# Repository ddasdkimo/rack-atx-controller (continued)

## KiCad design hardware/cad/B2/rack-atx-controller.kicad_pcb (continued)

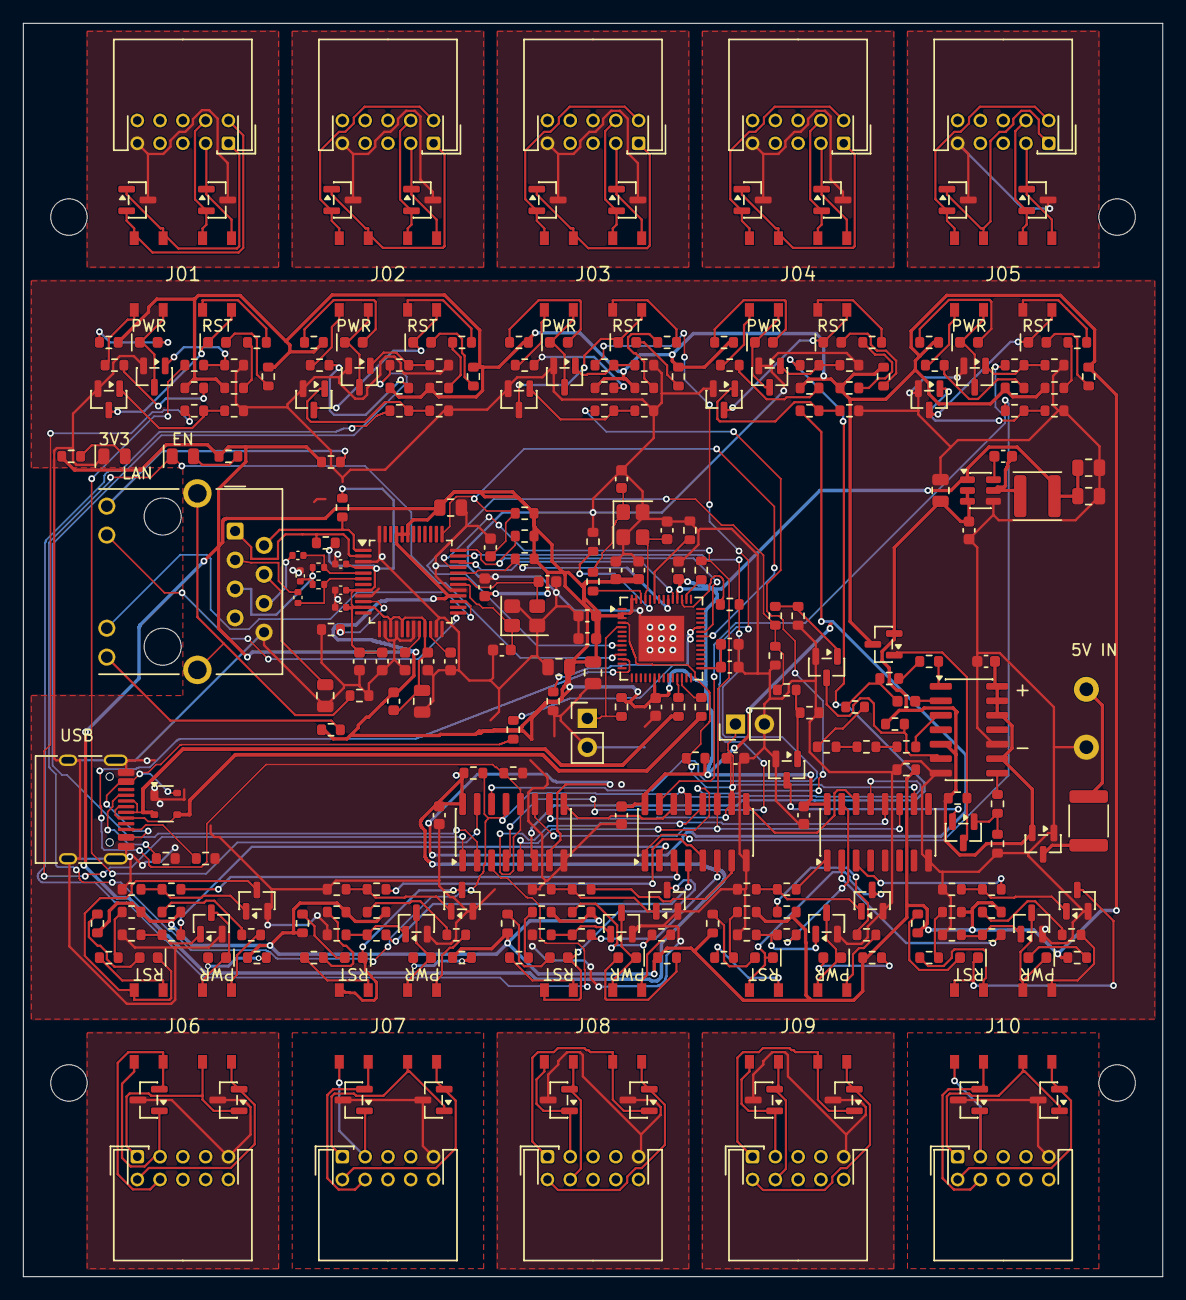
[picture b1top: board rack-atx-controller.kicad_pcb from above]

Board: 2 copper layers, 100.0 x 110.0 mm, 304 parts (0 on the bottom side), 243 nets.

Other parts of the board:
MH1, MH2, MH3, MH4: MountingHole_3.2mm_M3

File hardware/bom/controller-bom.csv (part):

Designator,Quantity per board,Comment,Manufacturer,MPN,LCSC Part #,Package,Footprint candidate,Library class,Assembly,PCBA mode,Observed stock,Checked at UTC,Source,Notes
J101,1,WJ500V-5.08-2P,Ningbo Kangnex Elec,WJ500V-5.08-2P,C8465,"Plugin,P=5.08mm",RackATX:WJ500V_5.08_2P,Extended,Wave Soldering,Economic and Standard,261906,2026-10-13T15:48:15.997975+00:00,https://jlcpcb.com/partdetail/C8465,Drawing/library candidate used in S.3; physical footprint and assembly DFM qualification pending.
F1,1,MF-MSMF150/24X-2 1.5A,BOURNS,MF-MSMF150/24X-2,C78695,1812,Fuse:Fuse_1812_4532Metric,Extended,SMT Assembly,Economic and Standard,6223,2026-10-13T15:22:31.648916+00:00,https://jlcpcb.com/partdetail/C78695,
"Q1,Q4",2,AO3401A,Alpha & Omega Semicon,AO3401A,C15127,SOT-23,Package_TO_SOT_SMD:SOT-23,Basic,SMT Assembly,Economic and Standard,631158,2026-10-13T15:24:52.156424+00:00,https://jlcpcb.com/partdetail/C15127,
"C1,C14,C15,C27,C29",5,10u,Samsung Electro-Mechanics,CL21A106KAYNNNE,C15850,0805,Capacitor_SMD:C_0805_2012Metric,Basic,SMT Assembly,Economic and Standard,4003857,2026-10-13T15:20:39.544599+00:00,https://jlcpcb.com/partdetail/C15850,
"C2,C3,C6,C8,C9,C10,C11,C12,C13,C21,C22,C23,C24,C25,C26,C28,C37,C38,C39,C42",20,100n,YAGEO,CC0603KRX7R9BB104,C14663,0603,Capacitor_SMD:C_0603_1608Metric,Basic,SMT Assembly,Economic and Standard,53307896,2026-10-13T15:20:39.536320+00:00,https://jlcpcb.com/partdetail/C14663,
U1,1,AP63203WU-7,Diodes Incorporated,AP63203WU-7,C780769,TSOT-23-6,Package_TO_SOT_SMD:TSOT-23-6,Extended,SMT Assembly,Economic and Standard,8099,2026-10-13T15:15:58.092399+00:00,https://jlcpcb.com/partdetail/C780769,
L1,1,4.7uH FNR4018S4R7MT,cjiang (Changjiang Microelectronics Tech),FNR4018S4R7MT,C167806,"SMD,4x4mm",Inductor_SMD:L_Changjiang_FNR4018S,Extended,SMT Assembly,Economic and Standard,7188,2026-10-13T15:18:09.856125+00:00,https://jlcpcb.com/partdetail/C167806,Drawing/library candidate used in S.3; physical footprint and assembly DFM qualification pending.
"C4,C5",2,22u,Samsung Electro-Mechanics,CL21A226MAQNNNE,C45783,0805,Capacitor_SMD:C_0805_2012Metric,Basic,SMT Assembly,Economic and Standard,3454275,2026-10-13T15:15:59.158144+00:00,https://jlcpcb.com/partdetail/C45783,
U2,1,ESP32-S3FN8,Espressif Systems,ESP32-S3FN8,C2913196,QFN-56-EP(7x7),Package_DFN_QFN:QFN-56-1EP_7x7mm_P0.4mm_EP4x4mm,Extended,SMT Assembly,Economic and Standard,2345,2026-10-13T15:12:40.649680+00:00,https://jlcpcb.com/partdetail/C2913196,
"C7,C16,C30",3,1u,Samsung Electro-Mechanics,CL10A105KB8NNNC,C15849,0603,Capacitor_SMD:C_0603_1608Metric,Basic,SMT Assembly,Economic and Standard,10311730,2026-10-13T15:46:51.366149+00:00,https://jlcpcb.com/partdetail/C15849,
"R1,R2,R3,R4,R15,R16,R17,R25,R27,R28,R30,R33,R37,R35,R36",15,10k 1%,UNI-ROYAL(Uniroyal Elec),0603WAF1002T5E,C25804,0603,Resistor_SMD:R_0603_1608Metric,Basic,SMT Assembly,Economic and Standard,31975394,2026-10-13T15:10:20.790070+00:00,https://jlcpcb.com/partdetail/C25804,
"J102,J103",2,PZ254V-11-02P,XFCN,PZ254V-11-02P,C492401,"Plugin,P=2.54mm",Connector_PinHeader_2.54mm:PinHeader_1x02_P2.54mm_Vertical,Extended,Wave Soldering,Economic and Standard,1143383,2026-10-13T15:31:20.503576+00:00,https://jlcpcb.com/partdetail/C492401,
Y1,1,40MHz CL12pF,YXC Crystal Oscillators,XL2EL89COI-111YLC-40M,C18214314,SMD3225-4P,Crystal:Crystal_SMD_3225-4Pin_3.2x2.5mm,Extended,SMT Assembly,Economic and Standard,31425,2026-10-13T15:20:35.889069+00:00,https://jlcpcb.com/partdetail/C18214314,
"R5,R24",2,0 1%,UNI-ROYAL(Uniroyal Elec),0603WAF0000T5E,C21189,0603,Resistor_SMD:R_0603_1608Metric,Basic,SMT Assembly,Economic and Standard,24624745,2026-10-13T15:20:39.483336+00:00,https://jlcpcb.com/partdetail/C21189,
"C17,C18,C31,C32",4,20p,Samsung Electro-Mechanics,CL10C200JB8NNNC,C1648,0603,Capacitor_SMD:C_0603_1608Metric,Basic,SMT Assembly,Economic and Standard,1984484,2026-10-13T15:22:34.155368+00:00,https://jlcpcb.com/partdetail/C1648,
"R6,R7",2,47 1%,UNI-ROYAL(Uniroyal Elec),0603WAF470JT5E,C23182,0603,Resistor_SMD:R_0603_1608Metric,Basic,SMT Assembly,Economic and Standard,971973,2026-10-13T15:11:27.450515+00:00,https://jlcpcb.com/partdetail/C23182,
J104,1,TYPE-C-31-M-12,Korean Hroparts Elec,TYPE-C-31-M-12,C165948,SMD,Connector_USB:USB_C_Receptacle_HRO_TYPE-C-31-M-12,Extended,SMT Assembly,Economic and Standard,398485,2026-10-13T15:11:33.015832+00:00,https://jlcpcb.com/partdetail/C165948,
D1,1,"PRTR5V0U2X,215",Nexperia,"PRTR5V0U2X,215",C12333,SOT-143,Package_TO_SOT_SMD:SOT-143,Extended,SMT Assembly,Economic and Standard,23665,2026-10-13T15:24:52.166312+00:00,https://jlcpcb.com/partdetail/C12333,
"R8,R9",2,5.1k 1%,UNI-ROYAL(Uniroyal Elec),0603WAF5101T5E,C23186,0603,Resistor_SMD:R_0603_1608Metric,Basic,SMT Assembly,Economic and Standard,24076196,2026-10-13T15:22:33.103748+00:00,https://jlcpcb.com/partdetail/C23186,
"R10,R11",2,33 1%,UNI-ROYAL(Uniroyal Elec),0603WAF330JT5E,C23140,0603,Resistor_SMD:R_0603_1608Metric,Basic,SMT Assembly,Economic and Standard,5175876,2026-10-13T15:41:21.024471+00:00,https://jlcpcb.com/partdetail/C23140,
"R12,R13,R26,R29,R31,R32,RT1,RT2,RT3,RT4,R34,R38,R40,R44,R48,R52,R56,R60,R64,R68,R72,R76,R80,R84,R88,R92,R96,R100,R104,R108,R112,R116",32,100k 1%,UNI-ROYAL(Uniroyal Elec),0603WAF1003T5E,C25803,0603,Resistor_SMD:R_0603_1608Metric,Basic,SMT Assembly,Economic and Standard,20296056,2026-10-13T15:11:26.198973+00:00,https://jlcpcb.com/partdetail/C25803,
U3,1,W5500,WIZNET,W5500,C32843,LQFP-48_7x7,Package_QFP:LQFP-48_7x7mm_P0.5mm,Extended,SMT Assembly,Economic and Standard,15204,2026-10-13T15:20:39.517626+00:00,https://jlcpcb.com/partdetail/C32843,
L2,1,120R@100MHz GZ1608D121TF,Sunlord,GZ1608D121TF,C12391,0603,Inductor_SMD:L_0603_1608Metric,Extended,SMT Assembly,Economic and Standard,211674,2026-10-13T15:31:21.203168+00:00,https://jlcpcb.com/partdetail/C12391,
R14,1,12.4k 1%,UNI-ROYAL(Uniroyal Elec),0603WAF1242T5E,C22865,0603,Resistor_SMD:R_0603_1608Metric,Extended,SMT Assembly,Economic and Standard,199175,2026-10-13T15:22:32.998707+00:00,https://jlcpcb.com/partdetail/C22865,
C19,1,4.7u,Samsung Electro-Mechanics,CL10A475KO8NNNC,C19666,0603,Capacitor_SMD:C_0603_1608Metric,Basic,SMT Assembly,Economic and Standard,3207024,2026-10-13T15:24:52.182713+00:00,https://jlcpcb.com/partdetail/C19666,
"C20,C33",2,10n,FH (Guangdong Fenghua Advanced Tech),0603B103K500NT,C57112,0603,Capacitor_SMD:C_0603_1608Metric,Basic,SMT Assembly,Economic and Standard,6247556,2026-10-13T15:22:34.255431+00:00,https://jlcpcb.com/partdetail/C57112,
Y2,1,25MHz CL12pF,YXC Crystal Oscillators,X322525MOB4SI,C9006,SMD3225-4P,Crystal:Crystal_SMD_3225-4Pin_3.2x2.5mm,Basic,SMT Assembly,Economic and Standard,181710,2026-10-13T15:18:09.304055+00:00,https://jlcpcb.com/partdetail/C9006,
"R18,R19,R20,R21",4,49.9 1%,UNI-ROYAL(Uniroyal Elec),0603WAF499JT5E,C23185,0603,Resistor_SMD:R_0603_1608Metric,Basic,SMT Assembly,Economic and Standard,1972323,2026-10-13T15:24:51.215319+00:00,https://jlcpcb.com/partdetail/C23185,
"C34,C35",2,6.8n,FH (Guangdong Fenghua Advanced Tech),0603B682K500NT,C1631,0603,Capacitor_SMD:C_0603_1608Metric,Basic,SMT Assembly,Economic and Standard,196089,2026-10-13T15:24:50.480062+00:00,https://jlcpcb.com/partdetail/C1631,
C36,1,22n,Samsung Electro-Mechanics,CL21B223KBANNNC,C1729,0805,Capacitor_SMD:C_0805_2012Metric,Basic,SMT Assembly,Economic and Standard,325000,2026-10-13T15:24:52.121389+00:00,https://jlcpcb.com/partdetail/C1729,
"R22,R23,R321,R322",4,330 1%,UNI-ROYAL(Uniroyal Elec),0603WAF3300T5E,C23138,0603,Resistor_SMD:R_0603_1608Metric,Basic,SMT Assembly,Economic and Standard,3627090,2026-10-13T15:12:44.845004+00:00,https://jlcpcb.com/partdetail/C23138,
J105,1,HR911105A,HANRUN(Zhongshan HanRun Elec),HR911105A,C12074,Plugin,Connector_RJ:RJ45_Hanrun_HR911105A_Horizontal,Extended,Wave Soldering,Economic and Standard,48875,2026-10-13T15:10:20.801373+00:00,https://jlcpcb.com/partdetail/C12074,
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
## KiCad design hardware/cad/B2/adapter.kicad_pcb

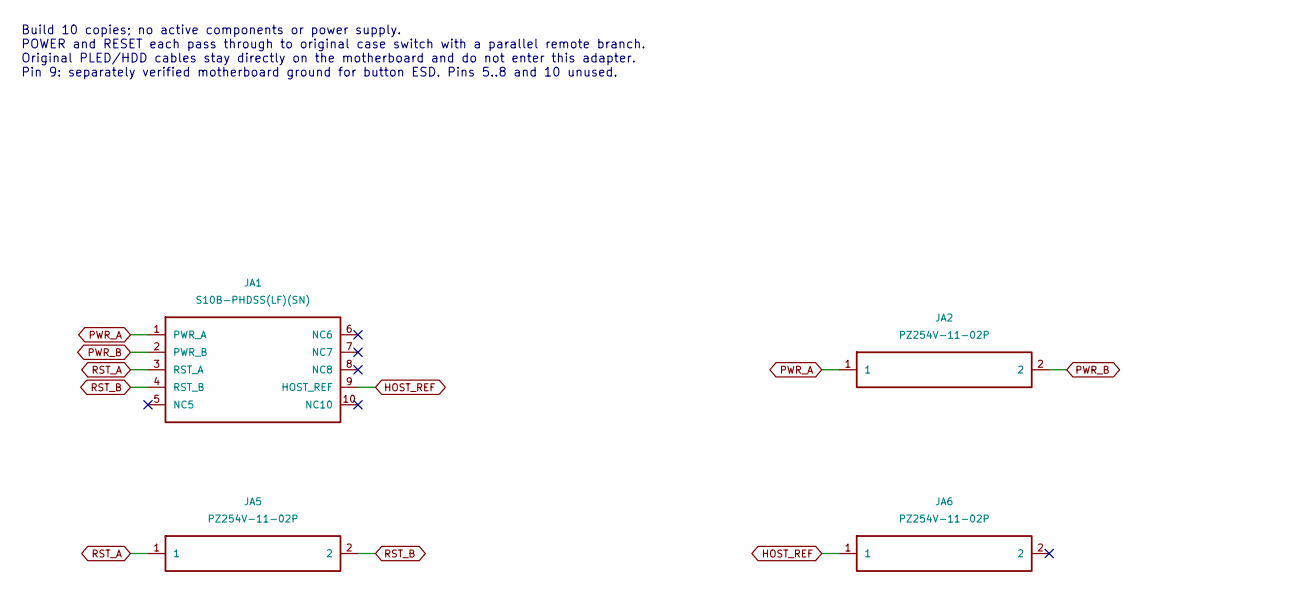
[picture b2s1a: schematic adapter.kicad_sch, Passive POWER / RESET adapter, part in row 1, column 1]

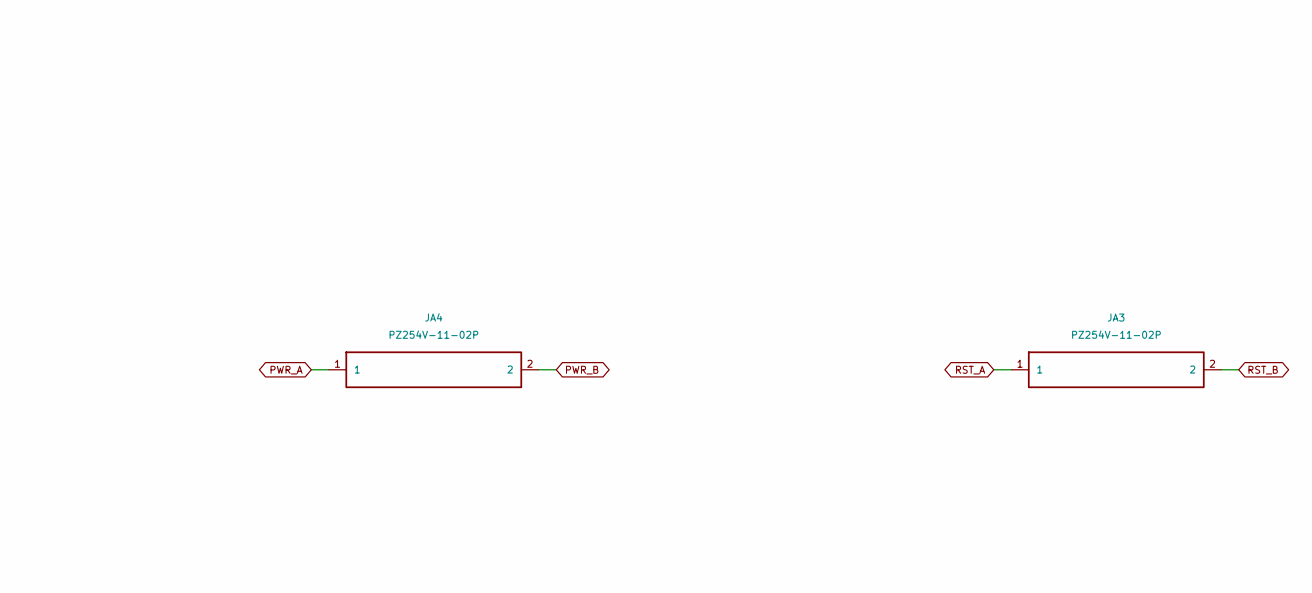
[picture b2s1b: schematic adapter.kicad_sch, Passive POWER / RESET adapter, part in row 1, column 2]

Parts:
JA1: S10B-PHDSS(LF)(SN); JST_PHD_S10B-PHDSS_2x05_P2.00mm_Horizontal; MPN S10B-PHDSS(LF)(SN); LCSC C161672
JA2, JA3, JA4, JA5, JA6: PZ254V-11-02P; PinHeader_1x02_P2.54mm_Vertical; MPN PZ254V-11-02P; LCSC C492401

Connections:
HOST_REF: JA1.9 (HOST_REF), JA6.1
PWR_A: JA1.1 (PWR_A), JA2.1, JA4.1
PWR_B: JA1.2 (PWR_B), JA2.2, JA4.2
RST_A: JA1.3 (RST_A), JA3.1, JA5.1
RST_B: JA1.4 (RST_B), JA3.2, JA5.2

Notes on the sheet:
Build 10 copies; no active components or power supply. POWER and RESET each pass through to original case switch with a parallel remote branch. Original PLED/HDD cables stay directly on the motherboard and do not enter this adapter. Pin 9: separately verified motherboard ground for button ESD. Pins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

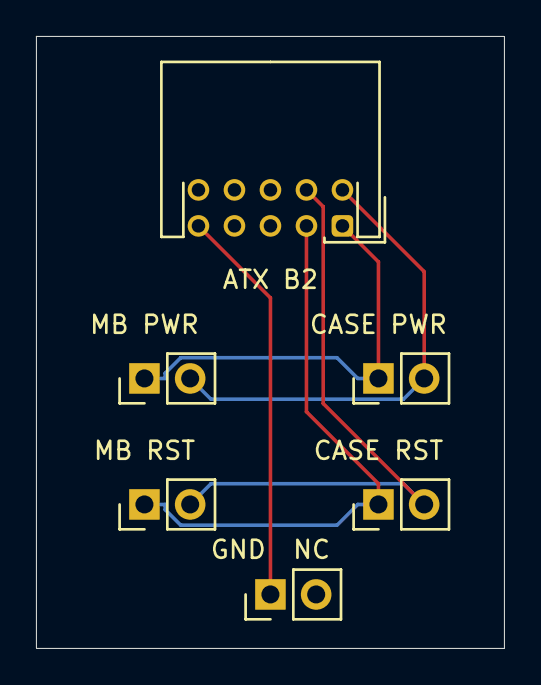
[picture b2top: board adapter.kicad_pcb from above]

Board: 2 copper layers, 26.0 x 34.0 mm, 6 parts (0 on the bottom side), 5 nets.

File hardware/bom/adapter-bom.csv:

Designator,Quantity per board,Comment,Manufacturer,MPN,LCSC Part #,Package,Footprint candidate,Library class,Assembly,PCBA mode,Observed stock,Checked at UTC,Source,Notes
JA1,1,S10B-PHDSS(LF)(SN),JST,S10B-PHDSS(LF)(SN),C161672,"Push-Pull,P=2mm",Connector_JST:JST_PHD_S10B-PHDSS_2x05_P2.00mm_Horizontal,Extended,Wave Soldering,Economic and Standard,9875,2026-10-13T15:20:39.554597+00:00,https://jlcpcb.com/partdetail/C161672,
"JA2,JA4,JA3,JA5,JA6",5,PZ254V-11-02P,XFCN,PZ254V-11-02P,C492401,"Plugin,P=2.54mm",Connector_PinHeader_2.54mm:PinHeader_1x02_P2.54mm_Vertical,Extended,Wave Soldering,Economic and Standard,1143383,2026-10-13T15:31:20.503576+00:00,https://jlcpcb.com/partdetail/C492401,
